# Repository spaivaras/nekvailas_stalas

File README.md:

Nekvailas Stalas
================

- **HardwareLayer** - Code for main hardware abstraction layer interfacing all sensors
- **pcb_nfc_antenna** - A KiCad project for multiple 125KHz pcb antennas
- **rfid_reader** - 125Khz I2C Atmega8 RFID reader
- **UI design** - Web page assets
- **api** - Web api

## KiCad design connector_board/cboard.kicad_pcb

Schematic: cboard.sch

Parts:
C1, C2, C3, C4, C5: 0.1uF
D1, D2, D3, D4: ZENERSMALL
P1, P2, P3, P5, P6, P7, P8, P9, P10, P11, P22: CONN_4
P4, P12, P13, P14, P15, P16, P17, P18, P19, P20, P21, P23, P24, P25, P26, P27, P28, P29, P30: CONN_2
Q1, Q2: BS107; TO92
R1, R2, R3, R4, R5, R6, R7, R8: 1K
R9, R12, R14, R16: 10K
R10, R11, R13, R15: 120

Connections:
+3.3V: P13.1, P17.1, P21.1, P26.1, P29.1, Q1.2 (G), Q2.2 (G), R1.1, R2.1, R9.1, R10.1, R11.1, R12.1, R13.1, R14.1, R15.1, R16.1
+5V: C1.1, C2.1, C3.1, C4.1, C5.1, P12.2 (PM), P16.2 (PM), P20.2 (PM), P25.2 (PM), P28.2 (PM), R3.1, R4.1
GND: C1.2, C2.2, C3.2, C4.2, C5.2, D1.1, D2.1, D3.1, D4.1, P1.2, P2.2, P5.2, P6.2, P7.2, P8.2, P10.2, P11.2, P12.1, P13.2 (PM), P14.2 (PM), P15.2 (PM), P16.1, P17.2 (PM), P18.2 (PM), P19.2 (PM), P20.1, P21.2 (PM), P23.2 (PM), P24.2 (PM), P25.1, P26.2 (PM), P27.2 (PM), P28.1, P29.2 (PM), P30.2 (PM)
unnamed: P3.1, P6.4
unnamed: P3.2, P5.4
unnamed: P2.4, P3.3
unnamed: P15.1, R10.2
unnamed: P1.4, P3.4
unnamed: P22.1, P30.1, R16.2
unnamed: P19.1, P22.3, R12.2
unnamed: P22.2, P24.1, R14.2
unnamed: P14.1, P22.4, R9.2
unnamed: P27.1, R15.2
unnamed: P23.1, R13.2
unnamed: P18.1, R11.2
unnamed: P7.3, P8.3, P10.3, P11.3, Q2.1 (D), R4.2
unnamed: P7.1, P8.1, P10.1, P11.1, Q1.1 (D), R3.2
unnamed: P1.1, P2.1, P4.2 (PM), P5.1, P6.1, Q1.3 (S), R1.2
unnamed: P1.3, P2.3, P4.1, P5.3, P6.3, Q2.3 (S), R2.2
unnamed: P11.4, R8.1
unnamed: P10.4, R7.1
unnamed: P8.4, R6.1
unnamed: D4.2, P9.1, R8.2
unnamed: D3.2, P9.2, R7.2
unnamed: D2.2, P9.3, R6.2
unnamed: D1.2, P9.4, R5.2
unnamed: P7.4, R5.1

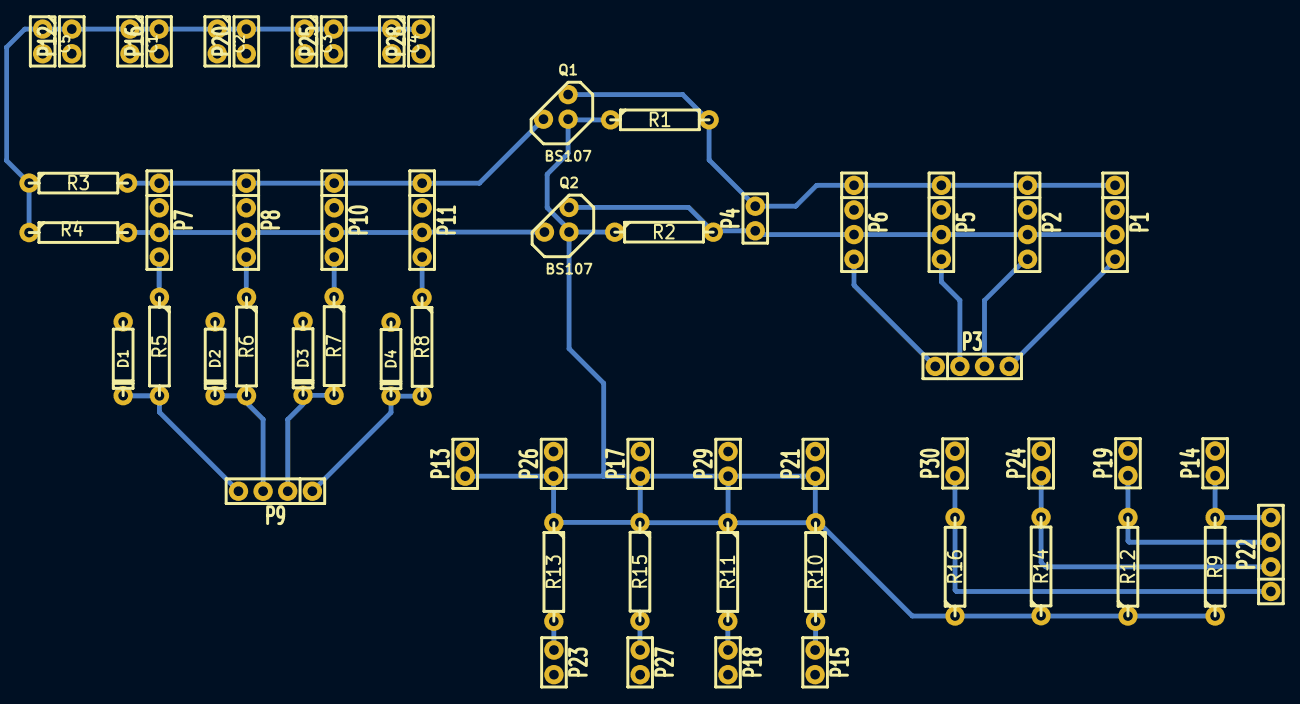
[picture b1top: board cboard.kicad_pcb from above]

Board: 2 copper layers, 57 parts (0 on the bottom side), 27 nets.

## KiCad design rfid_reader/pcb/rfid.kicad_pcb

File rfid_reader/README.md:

RFID Reader
=========

A simple 125KHz rfid reader based on a ATMega8

Build around a single timer (Timer1) uses 2 interrupts (INT0 and TIMER1_COMPA) transmits data via UART
Manchester code decoding based on Timing approach. Base clock 8MHz. On successful tag read the PB0 is raised HIGH
for 1 sec. In that time I2C routines are available to read the user ID.

------

Input
-------
- **PD2** (INT0) - Input of Card data (after amplifier)
- **PC5** - TWI SDC (internal pull-up)

Outputs
-------
- **PB1** - Carrier wave (125KHz square)
 - **PB0** - Interrupt after a successful tag read

Mixed
------
- **PC4** - TWI SDA (internal pull-up)

PCB
------
Single layer through-hole in KiCad format
 - Drill: 1 mm
 - Pads: 2mm
 - Tracks 0.4 mm

---
**Thanks to:**

- [Vassilis Serasidis](http://www.serasidis.gr/circuits/RFID_reader/125kHz_RFID_reader.htm) - RFID analog stuff, code ideas :)
- [Pascal Stang](http://www.procyonengineering.com/embedded/avr/avrlib/) - AVRLib

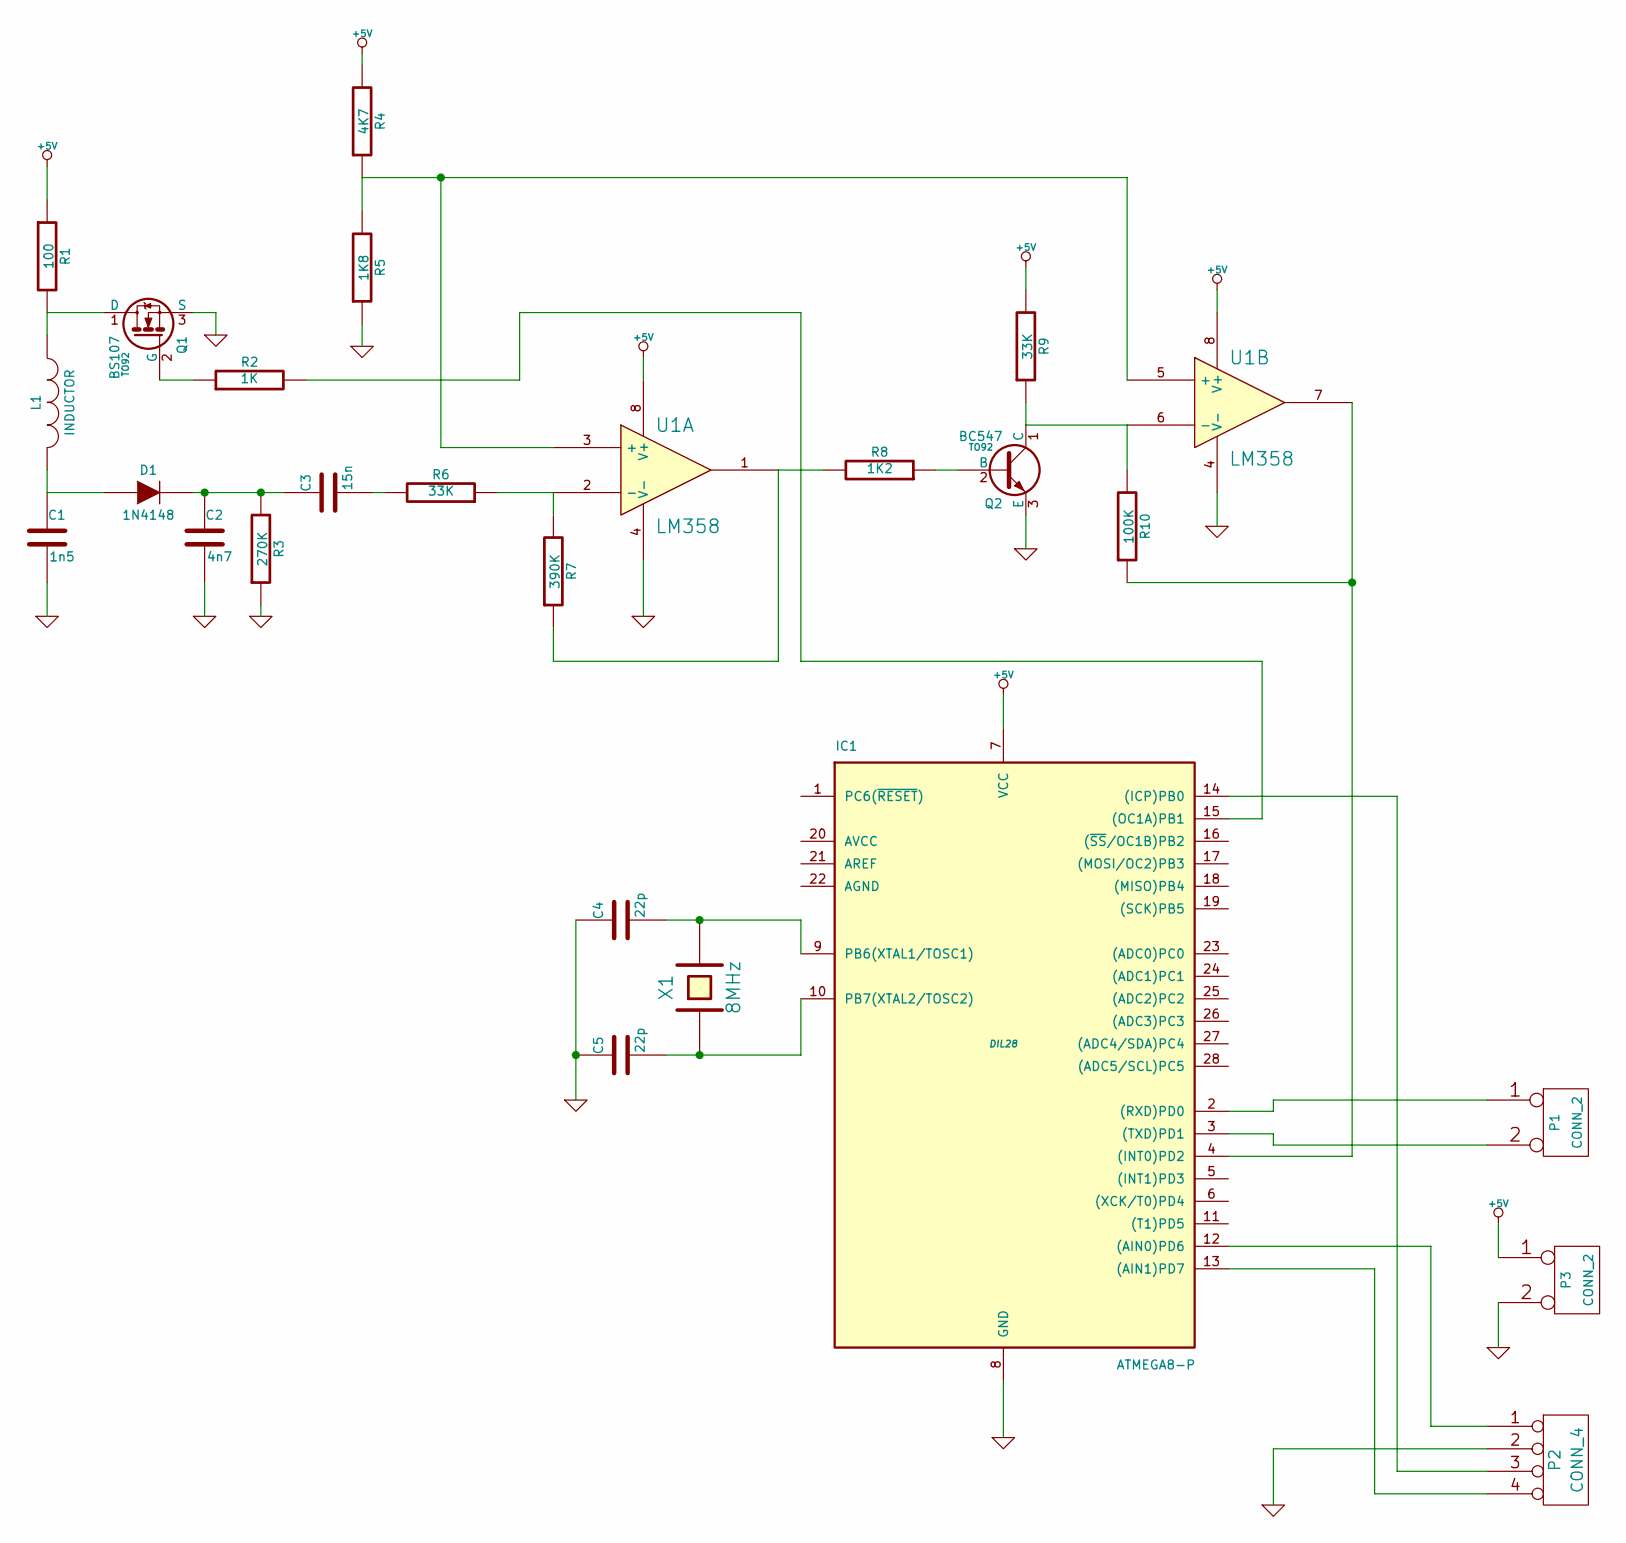
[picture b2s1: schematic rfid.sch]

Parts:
C1: 1n5
C2: 4n7
C3: 15n
C4, C5: 22p
D1: 1N4148
IC1: ATMEGA8-P; DIL28
L1: INDUCTOR
P1, P3: CONN_2
P2: CONN_4
Q1: BS107; TO92
Q2: BC547; TO92
R1: 100
R2: 1K
R3: 270K
R4: 4K7
R5: 1K8
R6, R9: 33K
R7: 390K
R8: 1K2
R10: 100K
U1: LM358
X1: 8MHz

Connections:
+5V: IC1.7 (VCC), P3.1, R1.1, R4.2, R9.2, U1.8 (V+)
GND: C1.2, C2.2, C4.1, C5.1, IC1.8 (GND), P2.2, P3.2 (PM), Q1.3 (S), Q2.3 (E), R3.1, R5.1, U1.4 (V-)
unnamed: IC1.4 ((INT0)PD2), R10.1, U1.7
unnamed: C5.2, IC1.10 (PB7(XTAL2/TOSC2)), X1.1
unnamed: C4.2, IC1.9 (PB6(XTAL1/TOSC1)), X1.2
unnamed: R6.1, R7.2, U1.2 (-)
unnamed: Q2.2 (B), R8.1
unnamed: R7.1, R8.2, U1.1
unnamed: Q2.1 (C), R9.1, R10.2, U1.6 (-)
unnamed: IC1.12 ((AIN0)PD6), P2.1
unnamed: IC1.14 ((ICP)PB0), P2.3
unnamed: IC1.13 ((AIN1)PD7), P2.4
unnamed: IC1.15 ((OC1A)PB1), R2.2
unnamed: IC1.3 ((TXD)PD1), P1.2 (PM)
unnamed: IC1.2 ((RXD)PD0), P1.1
unnamed: R4.1, R5.2, U1.3 (+), U1.5 (+)
unnamed: L1.1, Q1.1 (D), R1.2
unnamed: C3.2, R6.2
unnamed: Q1.2 (G), R2.1
unnamed: C1.1, D1.1 (A), L1.2
unnamed: C2.1, C3.1, D1.2 (K), R3.2

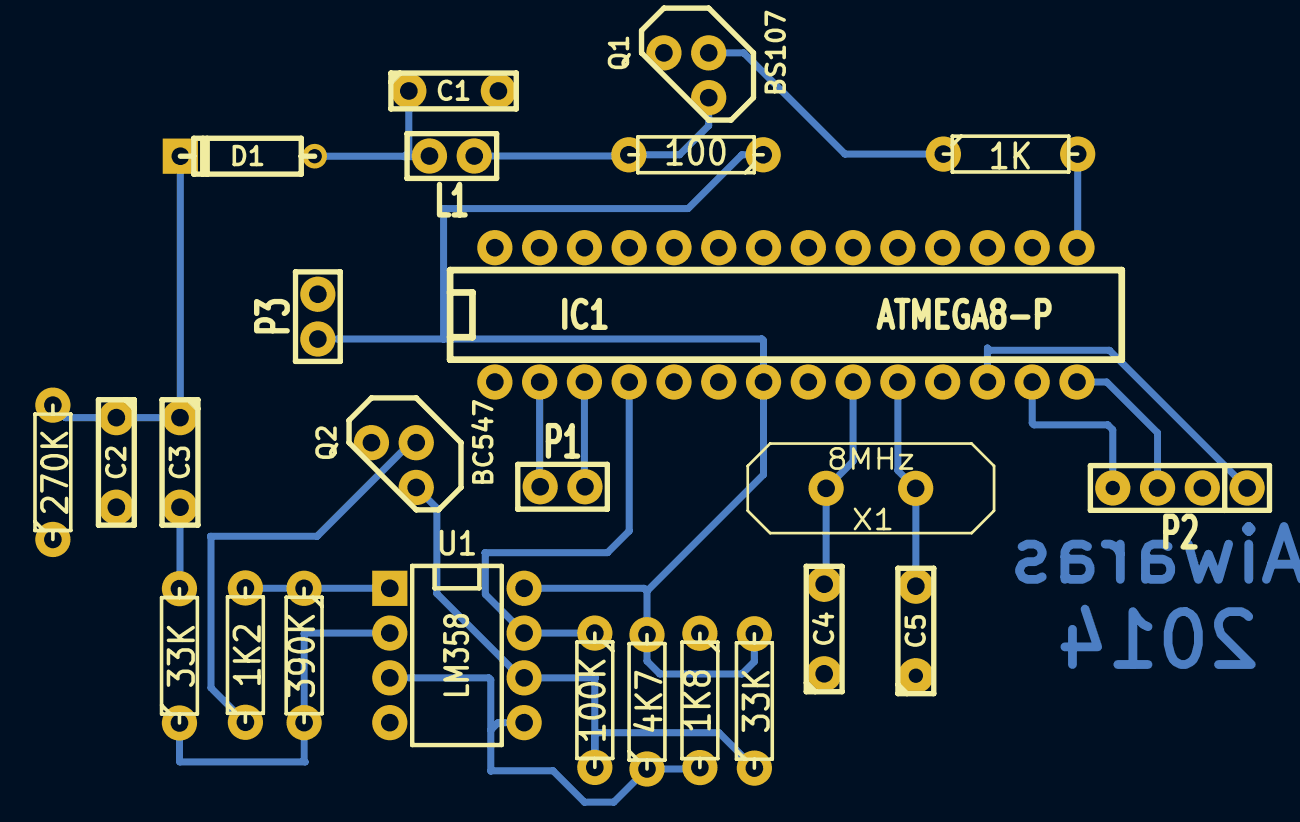
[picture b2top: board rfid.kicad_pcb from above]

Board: 2 copper layers, 25 parts (0 on the bottom side), 21 nets.

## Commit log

2014-04-15 adding gitignore with rules for kicad project
2014-04-15 adding two types of pcb antenna for RFID reader
2014-04-15 RFID reader initial commit
2014-04-15 Readme file for RFID
2014-04-15 What just happened?
2014-04-18 Adding source for controlling MPU6050 via RPi
2014-04-18 Adding additional credits
2014-04-21 Added I2C to PSB
2014-04-23 Updating source for I2C support
2014-04-23 Adding starting code for Hardwarelayer
2014-04-23 Updating readme's
2014-04-24 adding makefile for hardware-layer
2014-04-25 adding class for submitting table events
2014-04-26 web api skeleton
2014-04-26 adding events pusher on a separate thread
2014-04-27 Bug, unhandled i2c interrupt is streaching SCL
2014-04-27 Adding fatherboard
2014-04-27 sending events with real data!
2014-04-27 implementing very basic messages submission with curl
2014-04-28 updated .gitignore, added composer.lock
2014-04-28 updated api controllers
2014-04-28 adding more api requirements to HL readme
2014-04-28 adding content-type http header, fixes #10
2014-04-28 adding sleep in main loop to reduce CPU usage
2014-04-28 adding sleep functions
2014-04-28 api: added twig, updated composer, added templates, updated controller
2014-04-28 wraping outgoing message into json array
2014-04-28 adding project config.h
2014-04-28 moving remote API URL to config.h
2014-04-28 changing return codes to more common ones
2014-04-28 implementing signal handling
2014-04-28 updating sleep() to ignore nanoseconds
2014-04-29 api: ready for ox
2014-04-29 api: template ox fix
2014-04-29 updating remote API URL to production
2014-04-30 Adding gyro implementation, small changes
2014-04-30 Oops
2014-05-01 adding psiaudocode for morse encoder/sender with user callback
2014-05-01 Frontend base added
2014-05-01 Added DB support
2014-05-01 Fixed data format
2014-05-01 Revert mistake
2014-05-01 updated packages
2014-05-01 Adding goals
2014-05-02 getting MorseCoder class to compile, still segfoulting
2014-05-02 test db data
2014-05-02 getting MorseCoder work and even in asynchronous fashion!
2014-05-02 putting MorseCoder to use in project
2014-05-03 updating readme with AutoGoal event example
2014-05-03 adding logger to wrap around syslog and printf
2014-05-03 using wrapper macros for logging instead of plain printf()s
2014-05-03 added db rotate bash script
2014-05-03 api: updated events
2014-05-03 api: FUP 3b2e50c
2014-05-03 mysql delete from instead of truncate table
2014-05-04 adding init.d script to start daemon on system boot
2014-05-04 adding (un)install actions to makefile
2014-05-04 adding notes how to (un)install to readme file
2014-05-04 Removing security for make as root
2014-05-04 Adding some delays to GOAL!!!!
2014-05-04 Adding note on wolfram-engine
2014-05-05 UI screens and assets
2014-05-05 Added screen resolution
2014-05-05 Added extension
2014-05-05 Guest icon
2014-05-05 User profile picture placeholder
2014-05-05 Added page style
2014-05-05 Added users file
2014-05-05 Reverted times
2014-05-05 Removed comments
2014-05-06 Changed file name
2014-05-06 Added font weight
2014-05-06 Added not found user
2014-05-06 Removed border
2014-05-06 Changed guest image
2014-05-06 Fixed glitch effect
2014-05-06 Changing team layout
2014-05-06 api: update game logic
2014-05-06 api: update game logic #2
2014-05-06 api: update game logic #3
2014-05-06 Winners screen
2014-05-06 Added new assest and updated font instructions
2014-05-06 Adopted to different screen size
2014-05-06 Added winner layout
2014-05-06 Reset game after winning and if another goal is exist
2014-05-06 Updating HL documentation (pinouts)
2014-05-06 Removing outdated HL binary
2014-05-06 Little bit of cleanup
2014-05-06 cleaned php code to follow psr2 standard
2014-05-06 translation
2014-05-07 removed sql order
2014-05-07 Added fireworks
2014-05-07 Aliens!!!
2014-05-07 Added alien, fixed layout
2014-05-07 goals limited to 3
2014-05-07 Reverted last commit
2014-05-12 Removed top margin
2014-05-12 Changed layout
2014-05-12 Changed game reset logic
2014-05-14 Begin refactor code to services
2014-05-14 Removed fireworks
2014-05-14 Removed fireworks remains
2014-05-14 Refactor goes on
2014-05-17 Removed code to Provider class and controllers
2014-05-18 Moved logic to service
2014-05-18 Moved table logic to service
2014-05-20 Added user information tables to SQL
2014-05-23 Added user and card models, user repository
2014-05-24 Added base model
2014-05-24 Implemented using user repository
2014-05-25 Updated packages and added console component
2014-05-25 Added console command table:simulate
2014-05-26 Fixed event handler from hardware
2014-05-26 Changed database default charset
2014-05-26 Fixed user load from DB
2014-05-26 Implemented Table simulator, fixed bugs
2014-05-27 Begin implement user import command
2014-05-28 Implemented user import command
2014-05-29 Bug fixes
2014-08-09 Adding compiled hex file
2015-03-16 Created open API for students
2015-03-21 Added two GET parameters 'from-ts' and 'till-ts' on events list requests.
